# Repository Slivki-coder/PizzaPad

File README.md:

# PizzaPad
The PizzaPad is a small gadget designed to let you make pizza! It has a game that allows you to make your favorite kinds of pizzas and export your orders! You simply use a rotary encoder to cycle through the different toppings, and place them as needed.

The gadget was designed at Hack Club's Undercity Hackathon, held at Github HQ in San Francisco from July 11-14. 

[Here](https://youtu.be/aZLYuFsbn9c)'s a link to our demo.

# PCB
We decided that since this was a handheld device, we should try to make it as compact as possible and that'd be best done with a PCB. I designed a PCB in KiCAD within the constraints of the mill at Undercity (1 layer, 0.5 mm minimum trace, 0.5 mm minimum distance between traces, etc.). Here's the design of the milled PCB!

And here's the schematic!

# CAD
Oliver designed a case that would house the PCB, Screen, and Rotary Encoder. It's basically a little smaller than the size of the original 2DS. 

# GAME
The game is quite simple, with players creating their own pizzas and selecting the toppings and amount of toppings they'd like on it. Amounts and types of toppings would be controlled by rotating the encoder, while selecting would be controlled by the encoder's switch. In the end, the goal is to allow the player to export their pizza orders to remember them when they order pizza in real life in the future.

# BOM
- 1x Orpheus Pico or XIAO RP2040
- 1x KY-040 Rotary Encoder Switch
- 1x ILI9341 TFT Screen
- 1x 3D Printed Case with Top and Bottom Housings
- 1x PCB milled by @arp on Slack

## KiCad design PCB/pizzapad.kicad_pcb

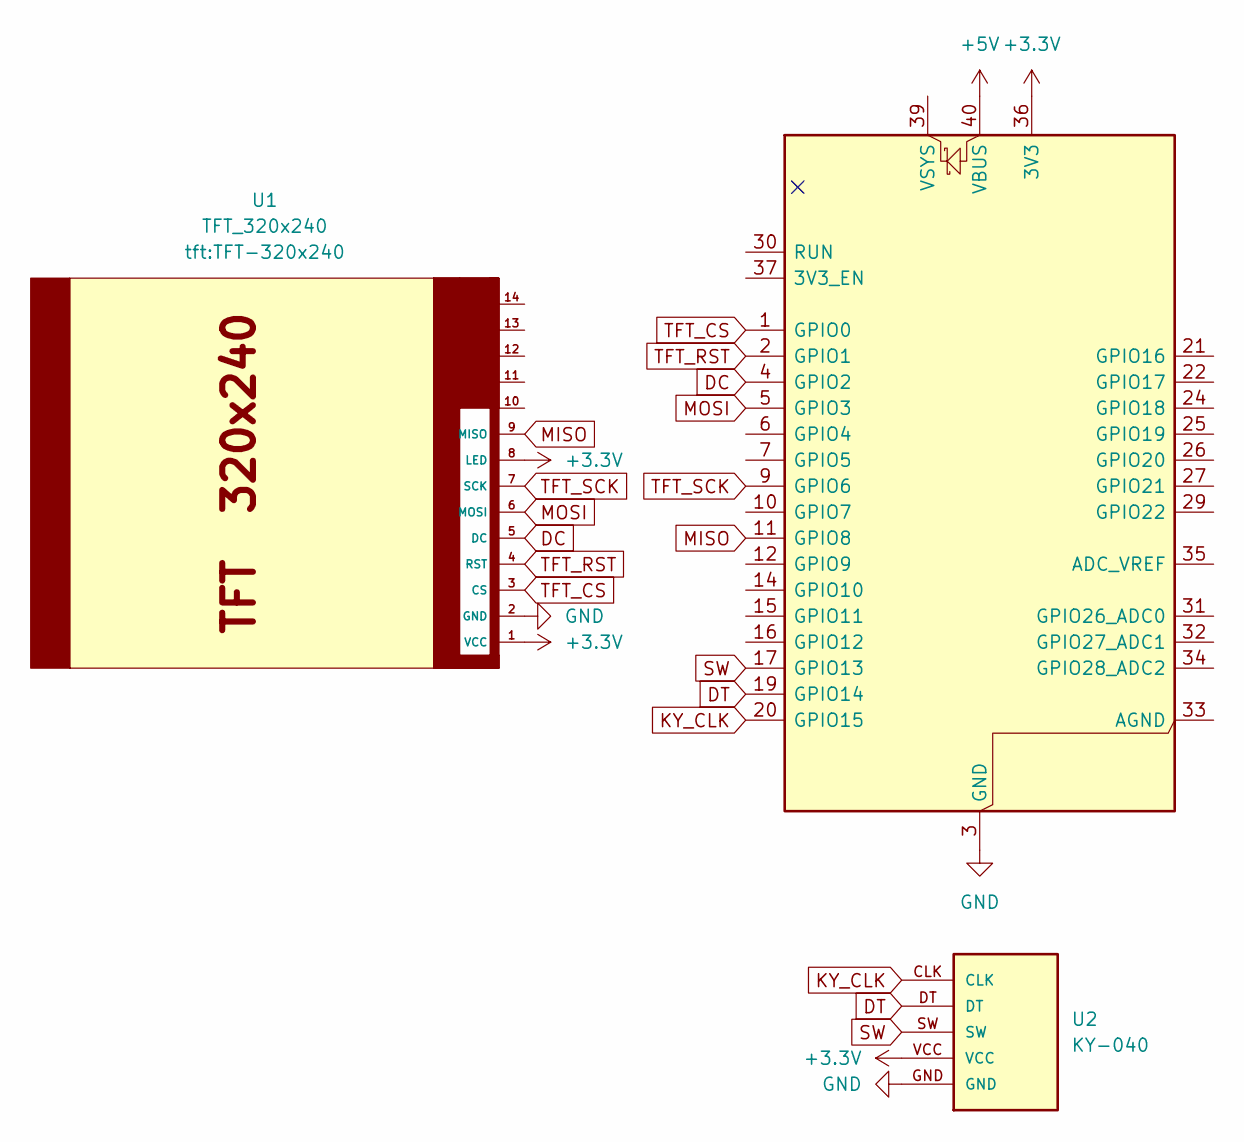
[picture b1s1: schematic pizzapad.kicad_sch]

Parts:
A1: RaspberryPi_Pico; RaspberryPi_Pico_Common_THT
U1: TFT_320x240; TFT-320x240
U2: KY-040; KY-040-PORT

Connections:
+3.3V: A1.36 (3V3), U1.1 (VCC), U1.8 (LED), U2.VCC
+5V: A1.40 (VBUS)
DC: A1.4 (GPIO2), U1.5 (DC)
DT: A1.19 (GPIO14), U2.DT
GND: A1.3 (GND), A1.8 (GND), A1.13 (GND), A1.18 (GND), A1.23 (GND), A1.28 (GND), A1.38 (GND), U1.2 (GND), U2.GND
KY_CLK: A1.20 (GPIO15), U2.CLK
MISO: A1.11 (GPIO8), U1.9 (MISO)
MOSI: A1.5 (GPIO3), U1.6 (MOSI)
SW: A1.17 (GPIO13), U2.SW
TFT_CS: A1.1 (GPIO0), U1.3 (CS)
TFT_RST: A1.2 (GPIO1), U1.4 (RST)
TFT_SCK: A1.9 (GPIO6), U1.7 (SCK)

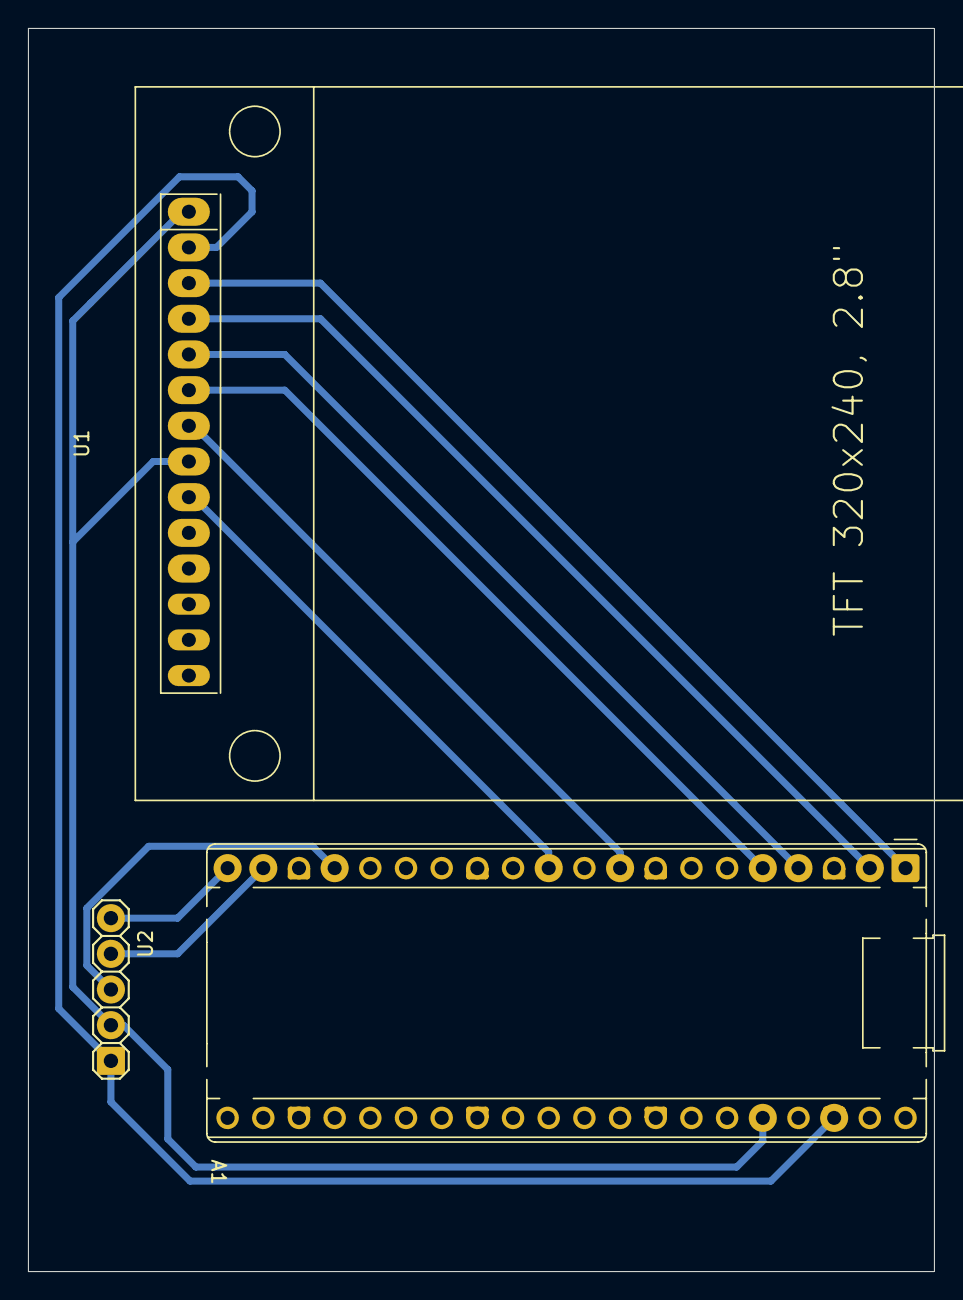
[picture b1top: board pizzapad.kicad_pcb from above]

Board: 2 copper layers, 64.5 x 88.5 mm, 3 parts (0 on the bottom side), 11 nets.

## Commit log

2025-07-13 added main.py
2025-07-13 added pcb step
2025-07-13 v3 pcb
2025-07-14 Added step files and f3z file for the case, cleaned up the folders a bit
2025-07-14 added production folder
2025-08-03 forgot to add push these
2025-08-06 new code, organization++
2025-08-06 fixed
2025-08-06 gerbers
2025-08-06 forgot to upload the bitmaps for the toppings
